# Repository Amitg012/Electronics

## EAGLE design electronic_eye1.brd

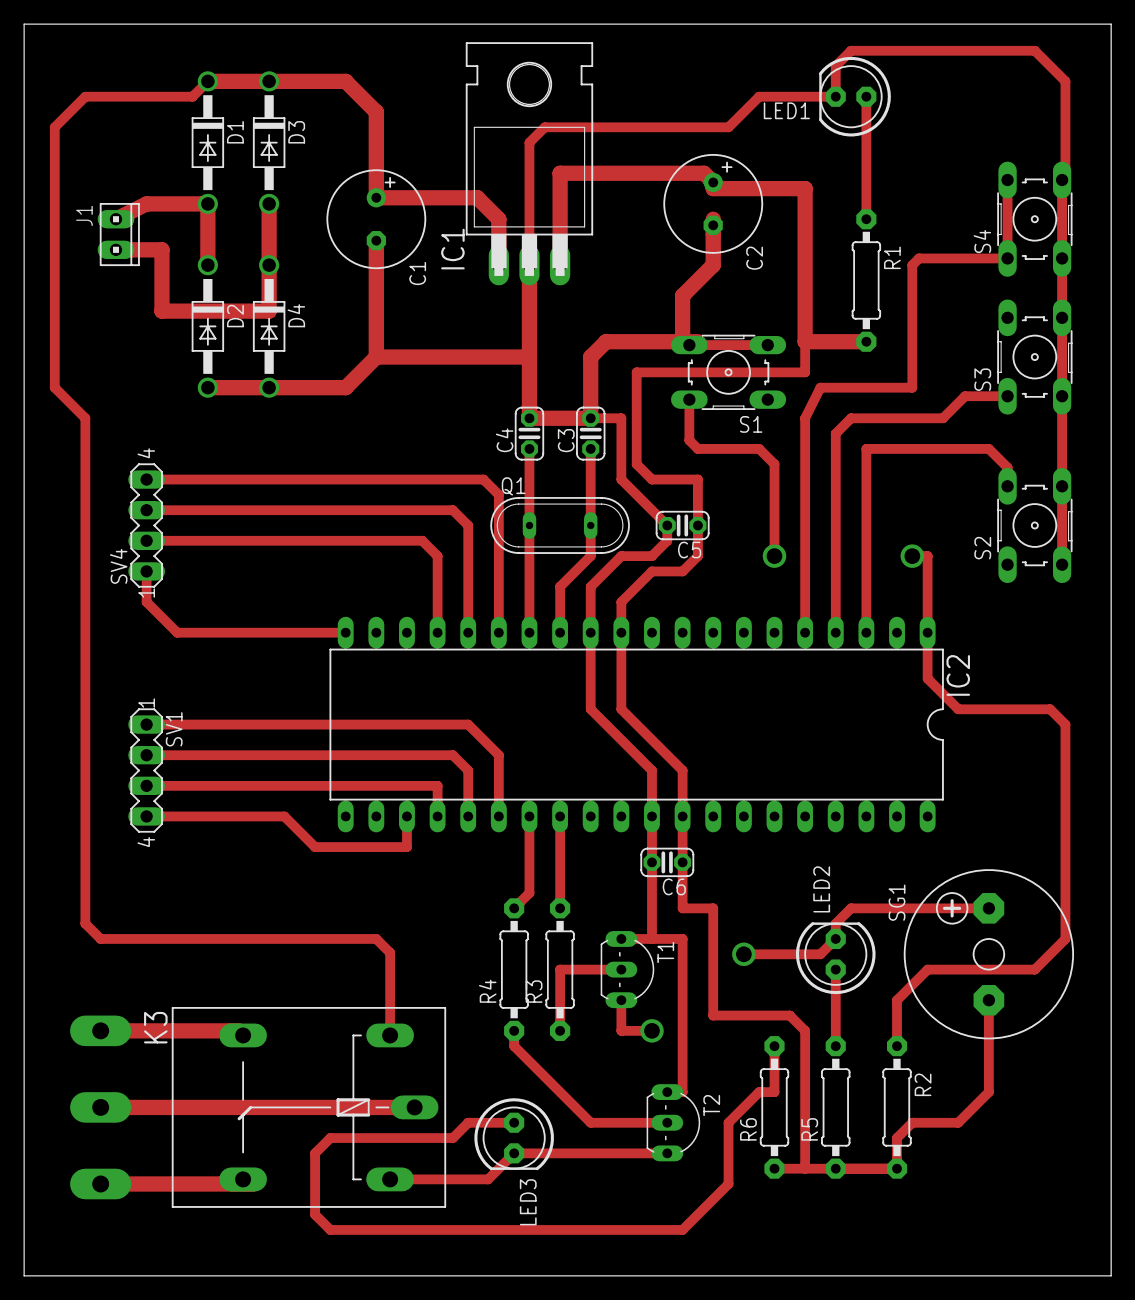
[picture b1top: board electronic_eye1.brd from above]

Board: 2 copper layers, 90.1 x 103.8 mm, 36 parts (0 on the bottom side), 31 nets.

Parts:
C1, C2: E3,5-8
C3, C4, C5, C6: C025-024X044
D1, D2, D3, D4: 1N4004; DO41-10
IC1: 7805T; TO220H
IC2: PIC18F4550_40; DIL40
J1: 10X02MTA
JP2, JP3, JP4: 1X1-BIGPOGO
K3: G5L; G5LE
LED1, LED2, LED3: LED5MM
Q1: QS
R1: 0207/10
R2, R3, R4, R5, R6: 10k; 0207/10
S1, S2, S3, S4: B3F-10XX
SG1: F/CM12P
SV1, SV4: MA04-1
T1, T2: 2N2222; TO92-EBC-OVAL

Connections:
+5V: C2.+, C5.1, C6.1, IC1.3, IC2.11, IC2.32, R1.2, R2.2, R5.1, R6.1, SG1.-
+12V: C1.+, D1.C, D3.C, IC1.1, K3.1
GND: C1.-, C2.-, C3.2, C4.2, C5.2, C6.2, D2.A, D4.A, IC1.2, IC2.12, IC2.31, LED1.K, S1.3, S1.4, S2.3, S2.4, S3.3, S3.4, S4.3, S4.4, T1.E, T2.E
unnamed: IC2.3, S2.2
unnamed: D1.A, D2.C, J1.2
unnamed: D3.A, D4.C, J1.1
unnamed: C4.1, IC2.14, Q1.1
unnamed: C3.1, IC2.13, Q1.2
unnamed: LED1.A, R1.1
unnamed: LED2.A, R5.2
unnamed: IC2.15, SV4.4
unnamed: R3.1, T1.B
unnamed: IC2.1, R2.1, S1.2
unnamed: R4.1, T2.B
unnamed: LED2.K, SG1.+, T1.C
unnamed: K3.2, LED3.K, T2.C
unnamed: LED3.A, R6.2
unnamed: JP4.P$1, K3.P
unnamed: JP2.P$1, K3.O
unnamed: JP3.P$1, K3.S
unnamed: IC2.16, SV4.3
unnamed: IC2.25, SV1.2
unnamed: IC2.26, SV1.1
unnamed: IC2.17, SV4.2
unnamed: IC2.20, SV4.1
unnamed: IC2.4, S3.1, S3.2
unnamed: IC2.5, S4.1, S4.2
unnamed: IC2.23, SV1.4
unnamed: IC2.27, R4.2
unnamed: IC2.28, R3.2
unnamed: IC2.24, SV1.3

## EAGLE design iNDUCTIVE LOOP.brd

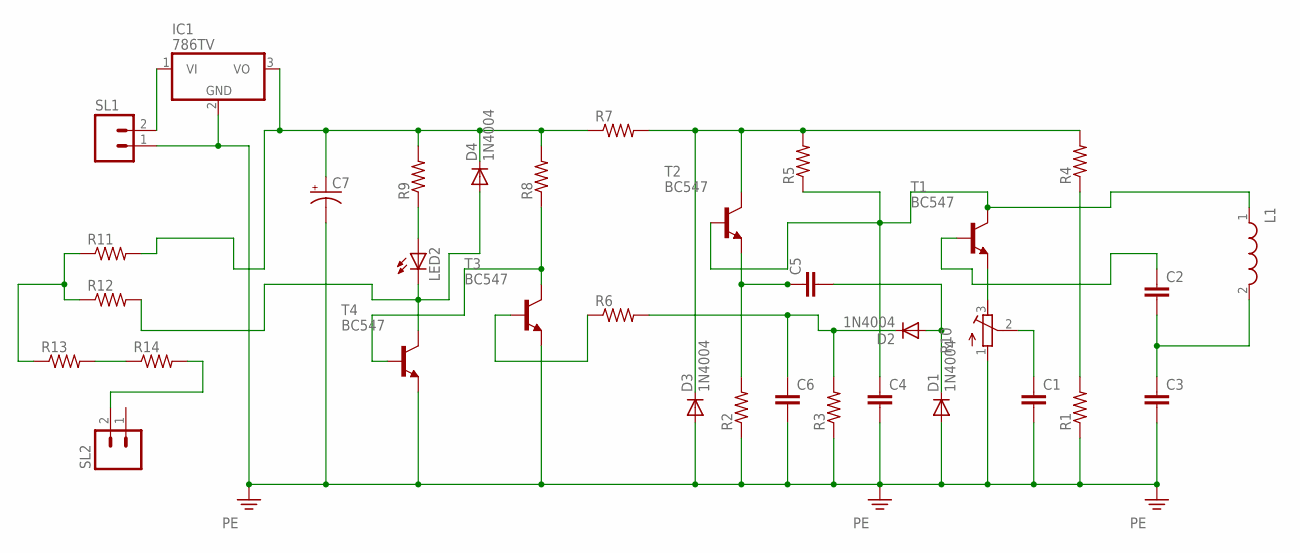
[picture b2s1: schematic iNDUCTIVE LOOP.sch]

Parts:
C1, C2, C3, C4, C5, C6: C5/2.5; C5B2.5
C7: CPOL-USE2.5-6; E2,5-6
D1, D2, D3, D4: 1N4004; DO41-10
IC1: 786TV; TO220V
L1: WE-WPCC_1W_3737; WE-WPCC_3737
LED2: LEDLD260; LD260
R1, R2, R3, R4, R5, R6, R7, R8, R9, R11, R12, R13, R14: R-US_0204/7; 0204/7
R10: R-TRIMM64P; RTRIM64P
SL1, SL2: MA02; 02PA
T1, T2, T3, T4: BC547; TO92

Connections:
unnamed: R11.1, R12.1, R13.1
unnamed: D3.C, R4.2, R5.2, R7.2, T2.3 (C)
unnamed: R6.1, T3.2 (B)
unnamed: C6.1, D2.C, R3.2, R6.2
unnamed: R8.1, T3.3 (C), T4.2 (B)
unnamed: LED2.A, R9.1
unnamed: IC1.1 (VI), SL1.2
unnamed: D4.A, LED2.K (C), R12.2, T4.3 (C)
unnamed: C5.1, R2.2, T2.1 (E)
unnamed: C4.1, L1.1, R5.1, T1.3 (C), T2.2 (B)
unnamed: C5.2, D1.C, D2.A
unnamed: R10.3 (E), T1.1 (E)
unnamed: C1.1, R10.2 (S)
unnamed: R1.2, R4.1
unnamed: C2.2, C3.1, L1.2
unnamed: C2.1, T1.2 (B)
unnamed: C7.+, D4.C, IC1.3 (VO), R7.1, R8.2, R9.2, R11.2
unnamed: R13.2, R14.1
unnamed: R14.2, SL2.2
PE: C1.2, C3.2, C4.2, C6.2, C7.-, D1.A, D3.A, IC1.2 (GND), R1.1, R2.1, R3.1, R10.1 (A), SL1.1, T3.1 (E), T4.1 (E)

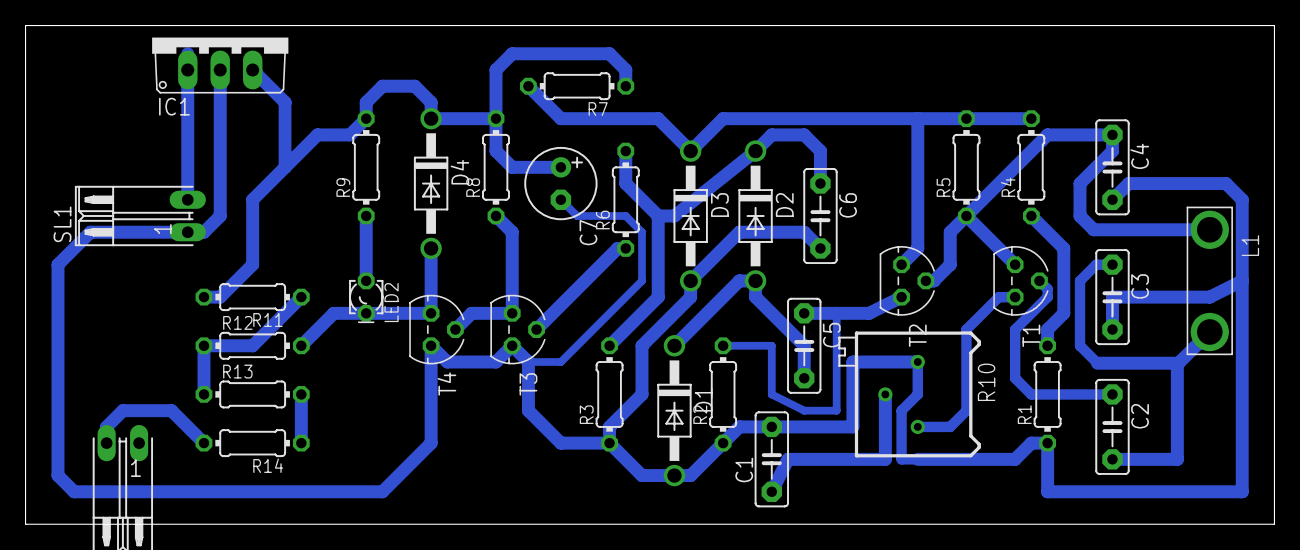
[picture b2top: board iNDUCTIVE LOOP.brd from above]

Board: 2 copper layers, 97.8 x 39.0 mm, 34 parts (0 on the bottom side), 20 nets.

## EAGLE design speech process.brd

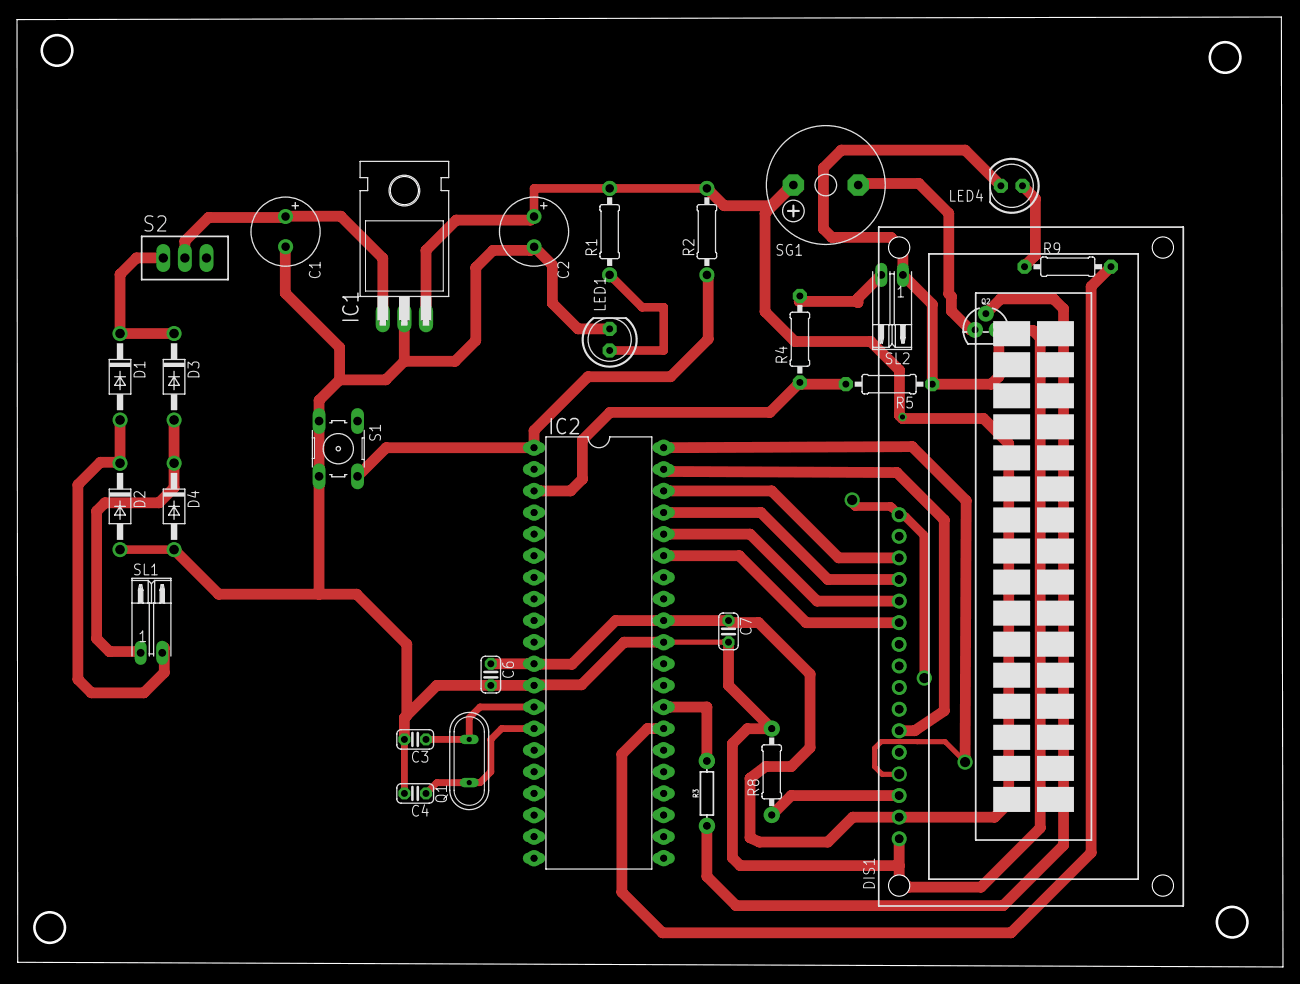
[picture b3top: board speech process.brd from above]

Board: 2 copper layers, 148.8 x 111.7 mm, 29 parts (0 on the bottom side), 24 nets.

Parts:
C1, C2: E3,5-8
C3, C4, C6, C7: C025-024X044
D1, D2, D3, D4: 1N4004; DO41-10
DIS1: TUXGR_16X2_R2
IC1: 7805T; TO220H
IC2: PIC18F4550_40; DIL40
LED1, LED4: LED5MM
Q1: QS
Q2: 600mA/40V; TO-92
R1: 0207/10
R2, R4, R5, R8: 10k; 0207/10
R3: 10k; AXIAL-0.3
R9: 470 E; 0207/10
S1: B3F-10XX
S2: TL37PO; TL3XPO
SG1: F/CM12P
SL1, SL2: 02PA

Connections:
+5V: C2.+, C6.1, C7.1, DIS1.2, DIS1.15, IC1.3, IC2.11, IC2.32, R1.2, R2.2, SG1.+
+12V: C1.+, IC1.1, S2.2
GND: C1.-, C2.-, C3.2, C4.2, C6.2, C7.2, D2.A, D4.A, DIS1.1, DIS1.5, DIS1.16, IC1.2, IC2.12, IC2.31, LED1.K, LED4.K, Q2.3, R5.1, R8.2, S1.3, S1.4, SL2.1
unnamed: D1.A, D2.C, SL1.2
unnamed: D3.A, D4.C, SL1.1
unnamed: LED1.A, R1.1
unnamed: DIS1.11, IC2.35
unnamed: R4.2, SL2.2
unnamed: IC2.28, R3.P$2
unnamed: IC2.1, R2.1, S1.2
unnamed: Q2.2, R3.P$1
unnamed: DIS1.4, IC2.40
unnamed: DIS1.6, IC2.39
unnamed: Q2.1, SG1.-
unnamed: IC2.27, R9.2
unnamed: LED4.A, R9.1
unnamed: IC2.3, R4.1, R5.2
unnamed: C4.1, IC2.14, Q1.1
unnamed: C3.1, IC2.13, Q1.2
unnamed: DIS1.14, IC2.38
unnamed: DIS1.13, IC2.37
unnamed: DIS1.12, IC2.36
unnamed: DIS1.3, R8.1
unnamed: D1.C, D3.C, S2.1

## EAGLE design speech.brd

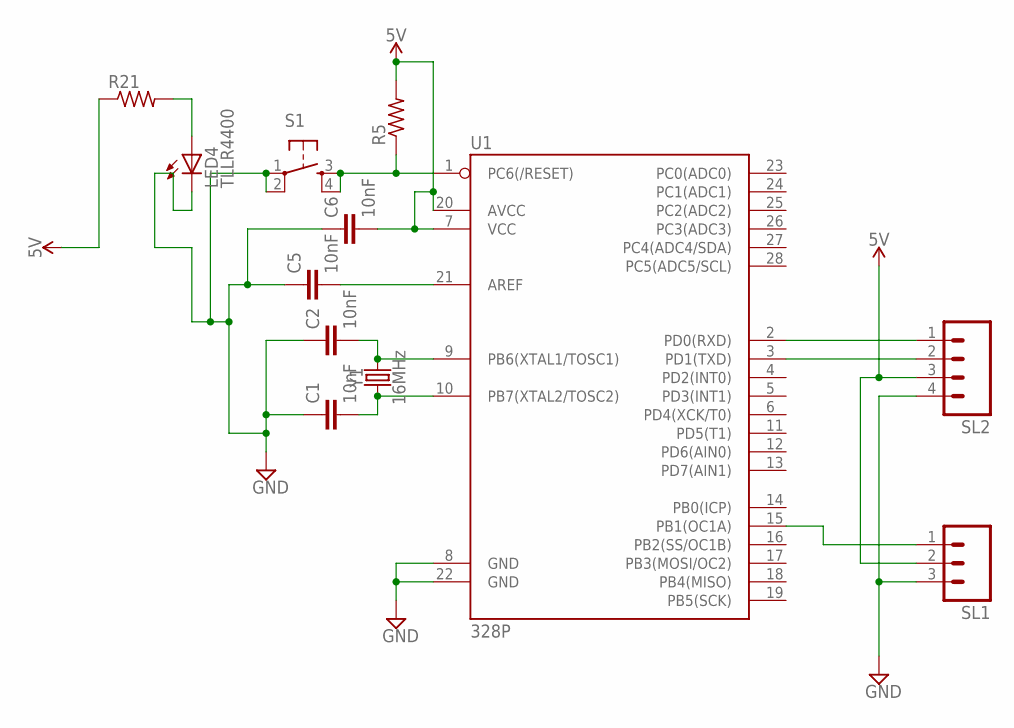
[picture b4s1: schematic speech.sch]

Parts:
C1, C2, C5, C6: 10nF; CAP-PTH-10MM
LED4: TLLR4400; LED3MM
R5, R21: R-US_0207/12; 0207/12
S1: TAC_SWITCHPTH; TACTILE-PTH
SL1: MA03; 03P
SL2: MA04; 04PA
U1: 328P; DIP28
Y1: 16MHz; HC49US

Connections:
5V: C6.2, R5.2, R21.1, SL1.2, SL2.3, U1.7 (VCC), U1.20 (AVCC)
GND: C1.1, C2.1, C5.1, C6.1, LED4.K (C), S1.1, S1.2, SL1.3, SL2.4, U1.8 (GND), U1.22 (GND)
unnamed: SL2.1, U1.2 (PD0(RXD))
unnamed: SL2.2, U1.3 (PD1(TXD))
unnamed: C2.2, U1.9 (PB6(XTAL1/TOSC1)), Y1.2
unnamed: C1.2, U1.10 (PB7(XTAL2/TOSC2)), Y1.1
unnamed: LED4.A, R21.2
unnamed: C5.2, U1.21 (AREF)
unnamed: SL1.1, U1.15 (PB1(OC1A))
unnamed: R5.1, S1.3, S1.4, U1.1 (PC6(/RESET))

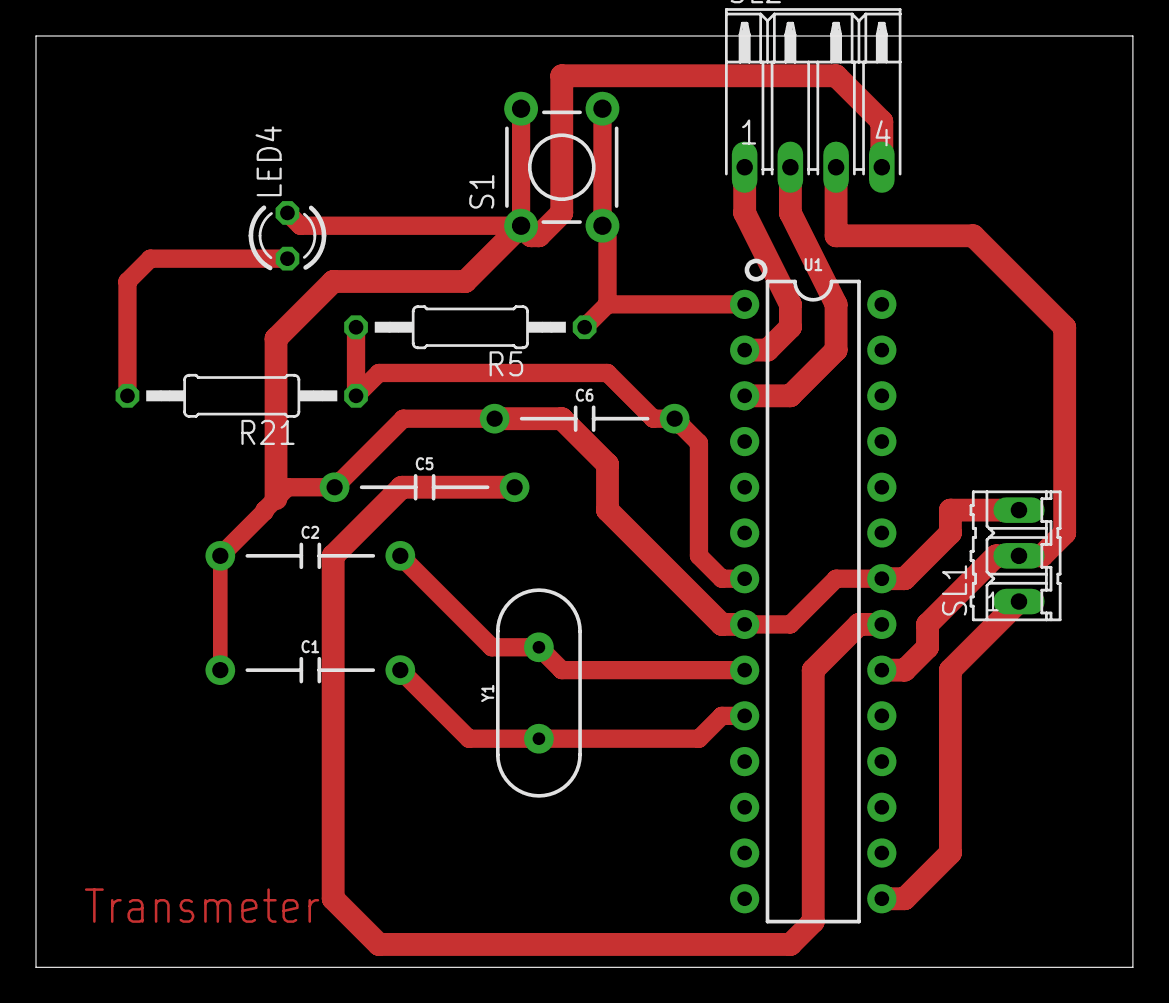
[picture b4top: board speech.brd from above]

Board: 2 copper layers, 60.9 x 51.7 mm, 12 parts (0 on the bottom side), 10 nets.

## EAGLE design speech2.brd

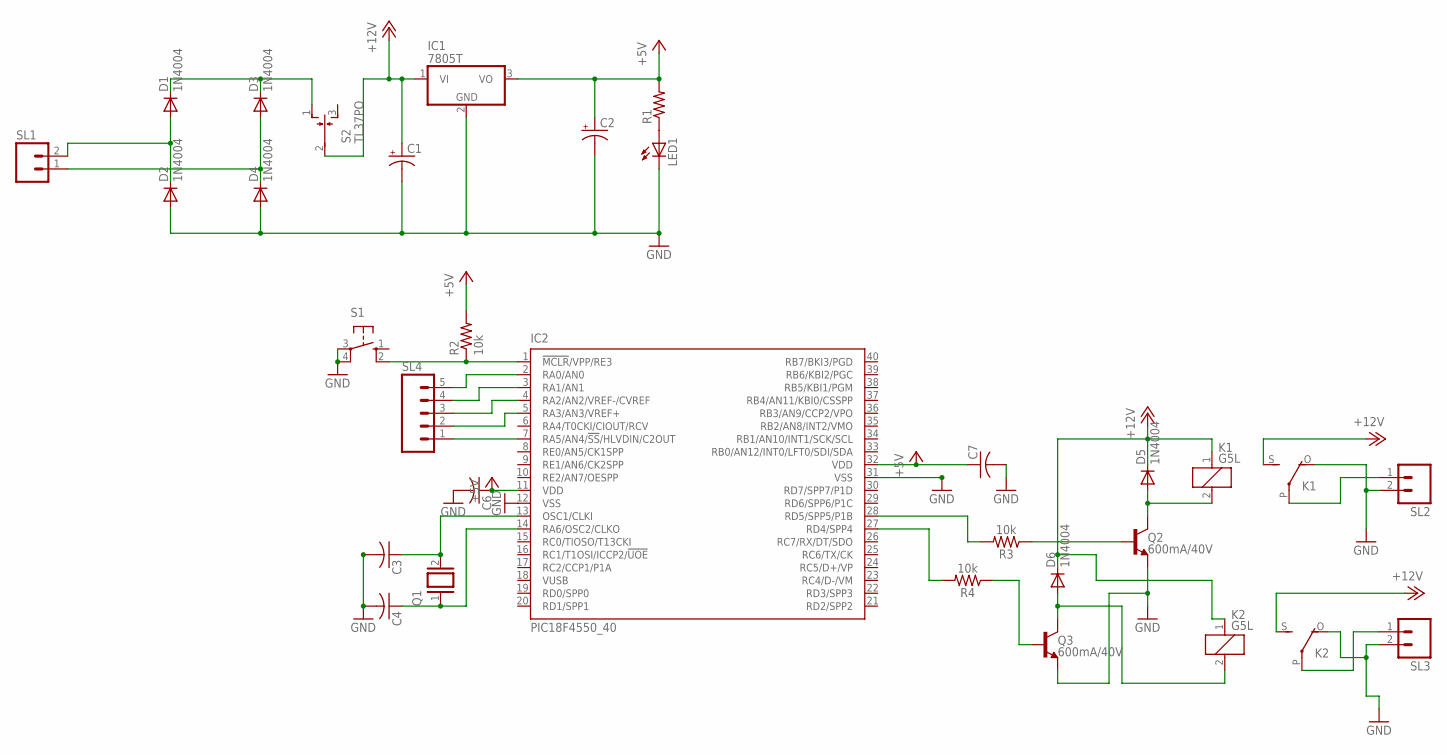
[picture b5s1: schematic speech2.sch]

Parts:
C1, C2: CPOL-USE3.5-8; E3,5-8
C3, C4, C6, C7: C-US025-024X044; C025-024X044
D1, D2, D3, D4, D5, D6: 1N4004; DO41-10
IC1: 7805T; TO220H
IC2: PIC18F4550_40; DIL40
K1, K2: G5L; G5LE
LED1: LED5MM
Q1: XTAL/S; QS
Q2, Q3: 600mA/40V; TO-92
R1: R-US_0207/10; 0207/10
R2: 10k; 0207/10
R3, R4: 10k; AXIAL-0.3
S1: 10-XX; B3F-10XX
S2: TL37PO; TL3XPO
SL1, SL2, SL3: MA02; 02PA
SL4: MA05; 05PA

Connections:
+5V: C2.+, C6.1, C7.1, IC1.3 (VO), IC2.11 (VDD), IC2.32 (VDD), R1.2, R2.2
+12V: C1.+, D5.C, D6.C, IC1.1 (VI), K1.1, K1.S, K2.1, K2.S, S2.2
GND: C1.-, C2.-, C3.2, C4.2, C6.2, C7.2, D2.A, D4.A, IC1.2 (GND), IC2.12 (VSS), IC2.31 (VSS), K1.O, K2.O, LED1.K (C), Q2.3 (E), Q3.3 (E), S1.3, S1.4 (P1), SL2.2, SL3.2
unnamed: D1.A, D2.C, SL1.2
unnamed: D3.A, D4.C, SL1.1
unnamed: IC2.27 (RD4/SPP4), R4.P$2 (2)
unnamed: Q3.2 (B), R4.P$1 (1)
unnamed: LED1.A, R1.1
unnamed: D5.A, K1.2, Q2.1 (C)
unnamed: IC2.2 (RA0/AN0), SL4.5
unnamed: IC2.28 (RD5/SPP5/P1B), R3.P$2 (2)
unnamed: IC2.1 (!MCLR!/VPP/RE3), R2.1, S1.2 (S1)
unnamed: Q2.2 (B), R3.P$1 (1)
unnamed: IC2.3 (RA1/AN1), SL4.4
unnamed: IC2.4 (RA2/AN2/VREF-/CVREF), SL4.3
unnamed: IC2.5 (RA3/AN3/VREF+), SL4.2
unnamed: D6.A, K2.2, Q3.1 (C)
unnamed: K2.P, SL3.1
unnamed: IC2.7 (RA5/AN4/!SS!/HLVDIN/C2OUT), SL4.1
unnamed: K1.P, SL2.1
unnamed: C4.1, IC2.14 (RA6/OSC2/CLKO), Q1.1
unnamed: C3.1, IC2.13 (OSC1/CLKI), Q1.2
unnamed: D1.C, D3.C, S2.1 (O)

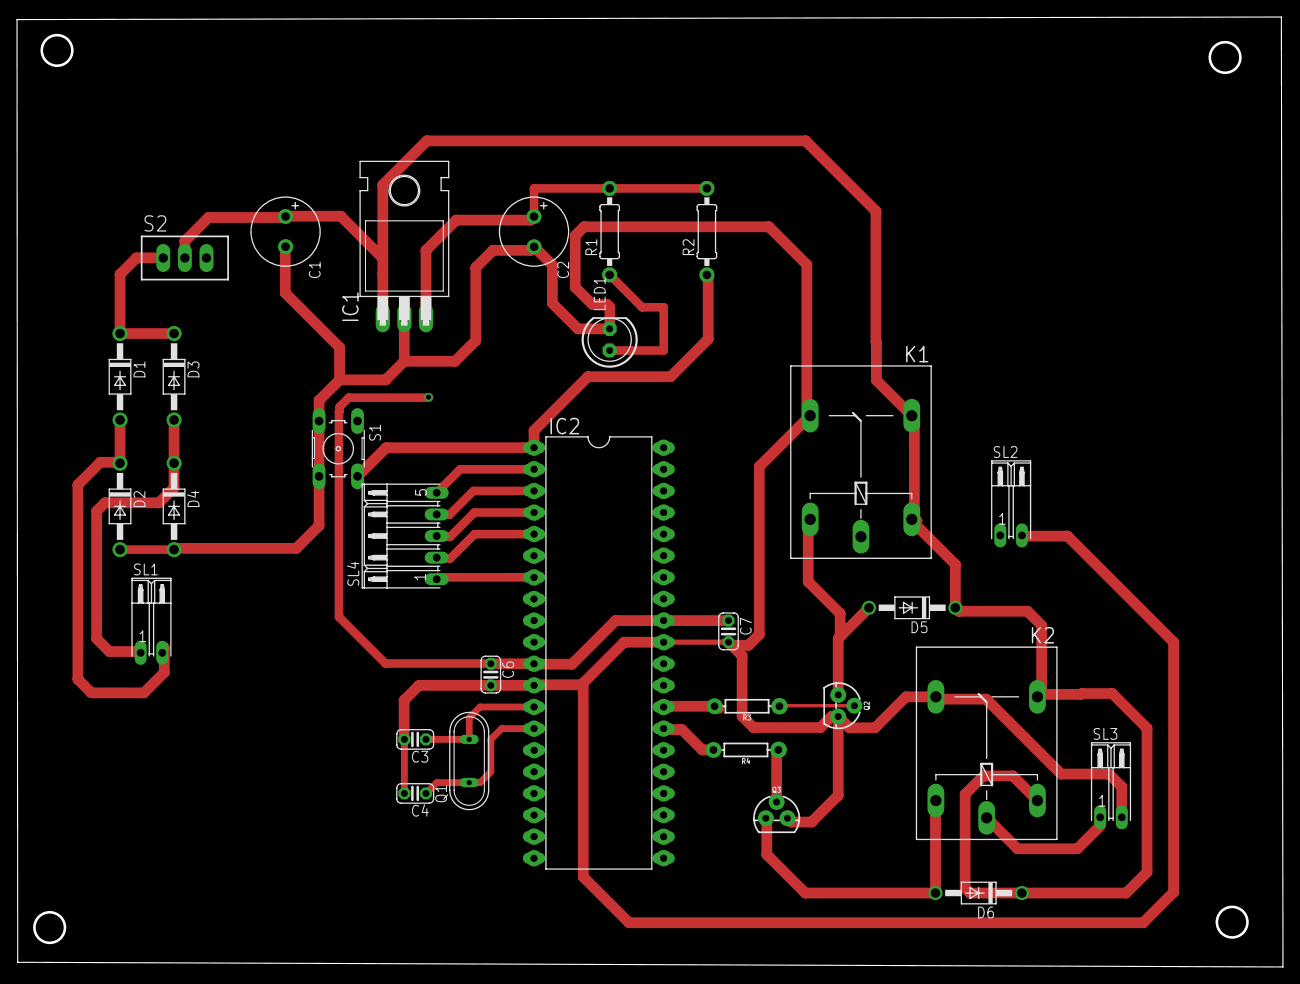
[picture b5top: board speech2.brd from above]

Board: 2 copper layers, 148.8 x 111.7 mm, 30 parts (0 on the bottom side), 23 nets.

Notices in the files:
parts and their libraries:
Wurth_Elektronik_Passive_rev15c: Copyright: Würth Elektronik
SparkFun-Resistors: Licensing: Creative Commons ShareAlike 4.0 International - https://creativecommons.org/licenses/by-sa/4.0
